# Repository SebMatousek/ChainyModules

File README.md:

# ChainyModules
An ecosystem of electronics modules based on the ESP32-C3FH4 microcontroller capable of chained communication through half-duplex UART.

This project is made to simplify the usage of different modules in robotics projects. Based on the microcontroller ESP32-C3FH4, which is powerfull enough for most tasks, different modules can be created, all the while allowing for chained connection (daisy chaining). Simply put, you can use these modules on different parts of your robot and interconnect them all using only 3 pins, and chain them together that only 1 cable needs to go to the main board (which can be a RPI, one of the modules themselves, ...).

Since all the modules use the same microcontroller, the programming is really easy and the communication as well -- the modules use half-duplex UART, the full-duplex UART from the ESP32 is transformed through a dual buffer open drain outputs. The absolute maximum speed for communication is 2,250,000 baud, but its better to use a bit less (1,000,000 baud works great and should be enough for most projects). For the programming of the boards, you can use the programming board specifically designed for this purpose so you don't have to connect 5 pins to each module separatly for programming.

The microcontroller has inbuilt flash for a smaller footprint on the board, and you can use WiFi or Bluetooth with it, it also has flash for storing user variables. It can also be connected to the computer directly without the need of a converter like the CP2102 (you may need to install a driver for it though).

Here are some more parameters:
|Chainy modules|v1.0|
|---|---|
| Microcontroller | ESP32-C3FH4 |
|Supply Voltage|3,3-12V|
|Communication pins|GND, VCC, TX|
|Maximum chained modules (limited by program only)|255|
|Broadcast ID|255|
|Currently designed modules|2|

### Instructions for using already existing modules
The already existing modules have their KiCAD schematic files in the Electronics/ folder. KiCAD 7.0.1 or newer is required, simply open the project and you should be able to plot the gerber files without having to modify anything.

The program is in the folder Software/ and is pretty simple. The basics for each module are the same and are in main.cpp. Every module has to be able to respond to the same basic commands (see table below). Specific modules then have different libraries with code to function. These libraries implement further commands, which have therefore preemptively been be added to the main.cpp switch statement.

|Command|cmd num|
|---|---|
|Set ID|1|
|Read type|2|
|Deepsleep*|3|

*Deepsleep is a command I implemented here because you can (and I did in one of my projects) use the power cables to also charge the robot when not running. Of course, this powers on the modules, so a module recognizes the charging (in my project that was simply using an LED and a photoresistor) and sends this command to the broadcasting address 255, so all the modules turn off. They then consume roughly 5 microamps so it doesn't slow down the charging nearly as much.

### Instructions for the custom servomotors
I created a custom servomotor capable of adressing and reading position, based on the MG90 servomotor. It uses the ChainyServo module board together with the two extension boards located inside the ChainyServo electronics folder. Using the picture in the ChainyServo Electronics folder, you can see how to assemble it. The STL and SLDPRT files are in the Mechanics/ folder. For the gears, motor and potentiometer, you can buy an MG90 (SG90 should work as well) servo and dissassemble it. When soldering the motor to the extension board, be careful that the dot on the plastic bottom of the motor has to align with the white arrow on the board, or the servo will rotate the other way and you will have to change the program. Also, beware that the motor can run on only about 5V, don't burn it - adjust the max pwm output accordingly!

I had my mechanical parts printed at JLCPCB with the material PA12.

#### Troubleshooting the servomotor
If the motor isn't spinning at all, most likely the mechanics is binding somewhere. Try to disassemble to servo and spin the gears manually a bit to see if you can find the problem.
If the motor spins but is going the wrong direction and won't stop jiggling, remove the biggest gear and flip it 180 degrees, which should fix the probelm (it can be inserted into the potentiometer in two ways but only one is correct).

### Instructions for creating a custom module
If you want to create a custom module to go with this repository, you are more than welcome to do so; and if you want send me the files and I can add them here, referencing you (pr not if you don't want me to).

To create a module that will be compatible, you have to mind these things the most:

|Dont't forget this|in your module|
|---|---|
| Microcontroller | ESP32-C3FH4 |
|Supply Voltage|3,3-12V*|
|Communication pins|GND, VCC, TX|
|Connectors|2x JST-PH|
|Programming pins (2mm connector)|VCC D+ D- BOOT GND**|
|Half duplex UART|at least 115 200 baud (ideally just use the buffer I have in my designs)|

*The range can be less if you want, but not more (or else you cannot use the modules already created). Ideally just use a regulator like the one in my modules.
** Or you can put a USB-C connector on the module but that's way too bulky and expensive for my liking.

Other than that, design what you like. You don't have to use my modules at all, as they probably don't fit your needs but that is fine --  the whole point of this project is to provide guidance on how to make such chained modules and to have some code and electronics done for it already, and over time hopefully create a whle ecosystem of these modules so that anyone can se what others have already designed and pick what souits them best. Have fun making, makers!

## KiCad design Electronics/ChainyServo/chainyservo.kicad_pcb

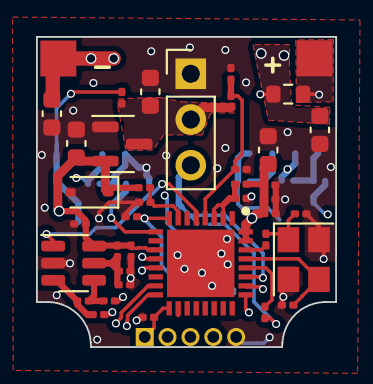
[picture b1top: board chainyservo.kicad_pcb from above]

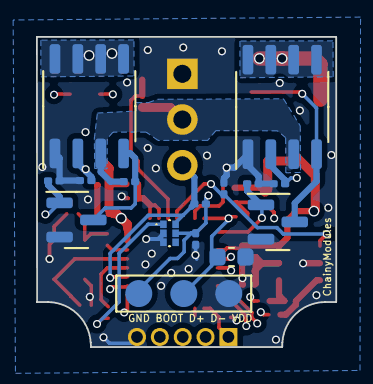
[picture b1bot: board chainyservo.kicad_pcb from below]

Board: 4 copper layers, 16.6 x 17.2 mm, 55 parts (15 on the bottom side), 29 nets.

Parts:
C1, C2, C7, C8, C9, C10, C13, C14, C17, C18, C19, C20: 100nF; C_0201_0603Metric
C3, C4: 27nF; C_0603_1608Metric
C5, C6, C21, C22: 2.2uF; C_0603_1608Metric
C11: 10nF; C_0201_0603Metric
C12: 1uF; C_0201_0603Metric
C15, C16: 16pF; C_0201_0603Metric
D1: BSD3C031V; D_SOD-323
IC1: ESP32-C3FH4; QFN50P500X500X90-33N-D
IC2: 74LVC2G07GM,132; PESD3V3L5UF115
J1: M+; Conn_pad_2x2mm
J2: Conn_01x03_Female; Pad_3_potentiometer
J3: Conn_01x03_Female; PinHeader_1x03_P2.54mm_Vertical
J4: Conn_01x05_Female; PinHeader_1x05_P1.27mm_Vertical
J5: M-; Conn_pad_2x2mm
L1: 2nH; L_0201_0603Metric
Q1, Q2: BSS138; SOT-23
R1, R3: 1k; R_0201_0603Metric
R2, R4, R5, R6, R10, R11, R15, R19: 22k; R_0201_0603Metric
R7: 10k; R_0201_0603Metric
R12, R14: 33R; R_0201_0603Metric
R13: 68m; R_0603_1608Metric
R16: 7k5; R_0201_0603Metric
R17: 0R; R_0201_0603Metric
R18: 499R; R_0201_0603Metric
U1, U2: WSP4606A; SOP-8_3.9x4.9mm_P1.27mm
U4: H7233-1; SOT-23
U5: INA181A1IDBVR; SOT-23-6
Y1: Crystal_GND23; Crystal_SMD_3225-4Pin_3.2x2.5mm

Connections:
+3V3: C2.1, C6.1, C9.1, C10.1, C11.1, C12.1, C13.1, C18.1, C21.1, D1.1 (K), IC1.11 (VDD3P3_RTC), IC1.17 (VDD3P3_CPU), IC1.31 (VDDA_1), IC1.32 (VDDA_2), IC2.5 (VCC), J2.1, J4.1, L1.1, R7.2, R10.1, R19.2, U4.2 (VO), U5.6 (V+)
AG1: IC1.9 (MTMS), Q1.1 (G), R5.1
AG2: IC1.16 (GPIO10), Q2.1 (G), R6.1
AMP: C20.1, IC1.5 (XTAL_32K_N), U5.1
BOOT: IC1.15 (GPIO9), J4.4
G1: Q1.3 (D), R1.2, U1.4 (G1)
G2: IC1.12 (MTCK), R2.1, U1.2 (G2)
G3: Q2.3 (D), R3.2, U2.4 (G1)
G4: IC1.13 (MTDO), R4.1, U2.2 (G2)
GND: C1.2, C2.2, C3.2, C4.2, C5.2, C6.2, C7.2, C9.2, C10.2, C11.2, C12.2, C13.2, C14.2, C15.2, C16.2, C17.2, C18.2, C19.2, C20.2, C21.2, C22.2, D1.2 (A), IC1.33 (GND), IC2.2 (GND), IC2.3 (2A), J2.3, J3.1, J4.5, Q1.2 (S), Q2.2 (S), R2.2, R4.2, R5.2, R6.2, R11.2, R16.2, U1.1 (S2), U2.1 (S2), U4.1 (GND), U5.2 (GND), Y1.2, Y1.4
M+: C4.1, R12.2, R13.1, U2.5 (D1), U2.6 (D1), U2.7 (D2), U2.8 (D2)
M-: C3.1, J5.1, U1.5 (D1), U1.6 (D1), U1.7 (D2), U1.8 (D2)
unnamed: C15.1, R17.2, Y1.1
unnamed: C17.1, IC1.7 (CHIP_EN), R19.1
unnamed: C14.1, IC1.2 (VDD3P3_1), IC1.3 (VDD3P3_2), L1.2
unnamed: IC2.1 (1A), R18.2
unnamed: J1.1, R13.2, R14.2
unnamed: C8.2, R14.1, U5.3 (+)
unnamed: C8.1, R12.1, U5.4 (-)
POT: C19.1, C22.1, IC1.8 (GPIO3), J2.2
REF: C7.1, R10.2, R11.1, U5.5 (REF)
RX: IC1.27 (U0RXD), IC2.6 (1Y), J3.3, R7.1
TX: IC1.28 (U0TXD), R18.1
USB_D+: IC1.26 (GPIO19), J4.2
USB_D-: IC1.25 (GPIO18), J4.3
VIN: C5.1, J3.2, R1.1, R3.1, R15.1, U1.3 (S1), U2.3 (S1), U4.3 (VI)
VM: C1.1, IC1.4 (XTAL_32K_P), R15.2, R16.1
XTAL_N: C16.1, IC1.29 (XTAL_N), Y1.3
XTAL_P: IC1.30 (XTAL_P), R17.1

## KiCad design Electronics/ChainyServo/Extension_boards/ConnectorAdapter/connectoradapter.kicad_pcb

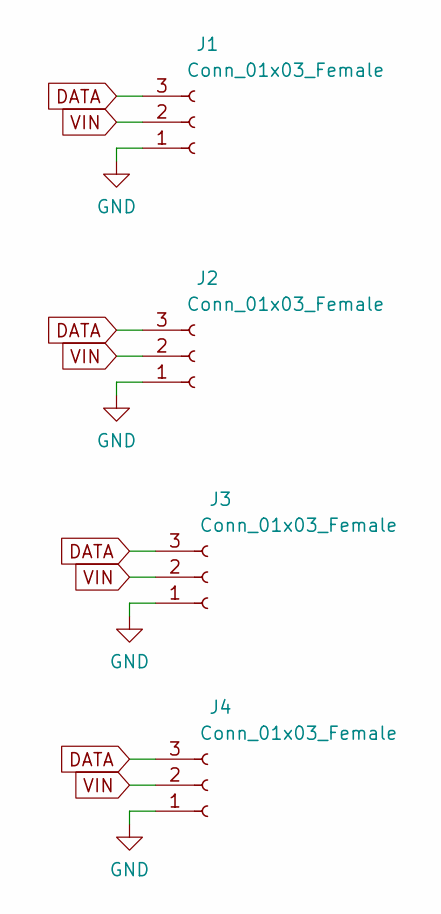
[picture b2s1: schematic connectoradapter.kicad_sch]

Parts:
J1: Conn_01x03_Female; PinHeader_1x03_P2.54mm_Vertical
J2, J3, J4: Conn_01x03_Female; JST_PH_S3B-PH-K_1x03_P2.00mm_Horizontal

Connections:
DATA: J1.3, J2.3, J3.3, J4.3
GND: J1.1, J2.1, J3.1, J4.1
VIN: J1.2, J2.2, J3.2, J4.2

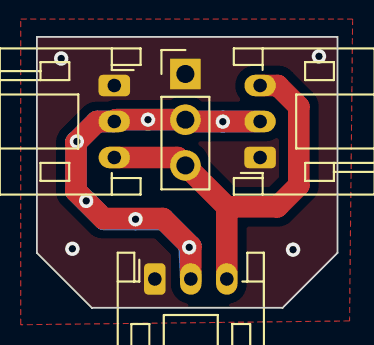
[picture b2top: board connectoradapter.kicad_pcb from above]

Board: 4 copper layers, 16.7 x 15.0 mm, 4 parts (0 on the bottom side), 3 nets.

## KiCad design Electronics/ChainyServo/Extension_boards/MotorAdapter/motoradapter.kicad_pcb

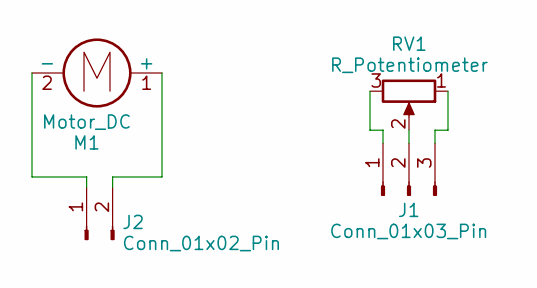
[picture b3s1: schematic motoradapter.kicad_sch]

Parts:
J1: Conn_01x03_Pin; PinHeader_1x03_P2.00mm_Vertical
J2: Conn_01x02_Pin; PinHeader_1x02_P2.00mm_Vertical
M1: Motor_DC; MG90I_motor
RV1: R_Potentiometer; MG90I_potentiometer

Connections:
unnamed: J1.1, RV1.3
unnamed: J1.2, RV1.2
unnamed: J1.3, RV1.1
unnamed: J2.1, M1.2 (-)
unnamed: J2.2, M1.1 (+)

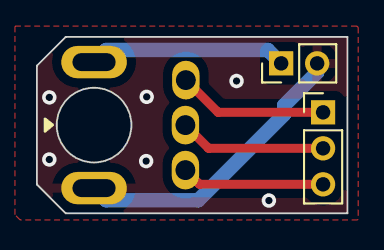
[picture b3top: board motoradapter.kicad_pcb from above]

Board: 4 copper layers, 17.2 x 9.8 mm, 4 parts (0 on the bottom side), 5 nets.

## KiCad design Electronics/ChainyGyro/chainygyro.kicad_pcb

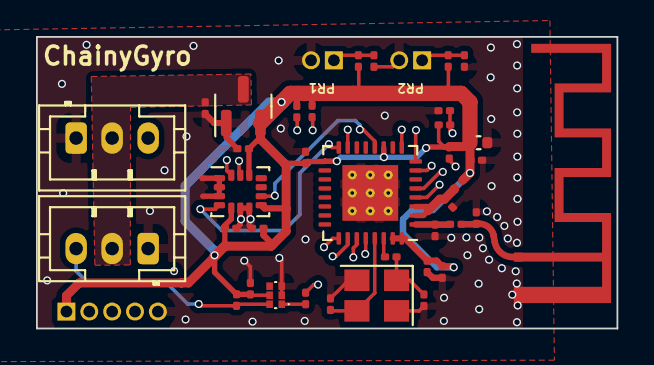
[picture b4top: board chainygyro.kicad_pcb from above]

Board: 4 copper layers, 32.2 x 16.2 mm, 40 parts (0 on the bottom side), 22 nets.

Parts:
AE1: PCB Antenna 2.4GHz 50Ohm; Texas_SWRA117D_2.4GHz_Left
C1, C3, C4, C6, C7, C12, C14, C17, C18, C19: 100nF; C_0201_0603Metric
C2: 10uF; C_0402_1005Metric
C5, C8: 16pF; C_0201_0603Metric
C9, C15, C16: 1uF; C_0201_0603Metric
C10: 10nF; C_0201_0603Metric
C11, C13: 3.3pF; C_0201_0603Metric
IC1: ESP32-C3FH4; QFN-32-1EP_5x5mm_P0.5mm_EP3.1x3.1mm_ThermalVias
IC2: 74LVC2G07GM,132; PESD3V3L5UF115
J1, J2: Conn_01x03_Female; JST_PH_B3B-PH-K_1x03_P2.00mm_Vertical
J3: Conn_01x05_Female; PinHeader_1x05_P1.27mm_Vertical
J4, J5: Conn_01x02_Socket; PinHeader_1x02_P1.27mm_Vertical
L1: 2nH; L_0201_0603Metric
L2: 2.2nH; L_0201_0603Metric
R1: 0R; R_0201_0603Metric
R2: 22k; R_0201_0603Metric
R3, R4, R6, R7, R8: 10k; R_0201_0603Metric
R5: 499R; R_0201_0603Metric
U1: H7233-1; SOT-23
U2: LSM6DS3TR-C; LGA-14_3x2.5mm_P0.5mm_LayoutBorder3x4y
Y1: Crystal_GND23; Crystal_SMD_3225-4Pin_3.2x2.5mm

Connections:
+3V3: C2.1, C4.1, C9.1, C10.1, C12.1, C14.1, C16.1, C17.1, C18.1, C19.1, IC1.11 (VDD3P3_RTC), IC1.17 (VDD3P3_CPU), IC1.31 (VDDA_1), IC1.32 (VDDA_2), IC2.5 (VCC), J3.1, L1.1, R2.2, R3.1, R4.1, R6.2, R7.1, R8.1, U1.2 (VO), U2.5 (VDDIO), U2.8 (VDD), U2.12 (CS)
BOOT: IC1.15 (GPIO9), J3.4
GND: AE1.1, C1.2, C2.2, C3.2, C4.2, C5.2, C6.2, C7.2, C8.2, C9.2, C10.2, C11.2, C12.2, C13.2, C14.2, C15.2, C16.2, C17.2, C18.2, C19.2, IC1.33 (GND), IC2.2 (GND), IC2.3 (2A), J1.1, J2.1, J3.5, J4.2, J5.2, U1.1 (GND), U2.1 (SDO/SA0), U2.2 (SDX), U2.3 (SCX), U2.6 (GND), U2.7 (GND), Y1.2, Y1.4
INT1: IC1.16 (GPIO10), U2.4 (INT1)
INT2: IC1.12 (MTCK), U2.9 (INT2)
LNA: C11.1, IC1.1 (LNA_IN), L2.1
unnamed: AE1.2, C13.1, L2.2
unnamed: C5.1, R1.2, Y1.1
unnamed: C7.1, IC1.7 (CHIP_EN), R2.1
unnamed: C6.1, IC1.2 (VDD3P3_1), IC1.3 (VDD3P3_2), L1.2
unnamed: IC2.1 (1A), R5.2
PR1: C1.1, IC1.9 (MTMS), J5.1, R4.2
PR2: C3.1, IC1.8 (GPIO3), J4.1, R3.2
RX: IC1.27 (U0RXD), IC2.6 (1Y), J1.3, J2.3, R6.1
SCL: IC1.4 (XTAL_32K_P), R7.2, U2.13 (SCL)
SDA: IC1.5 (XTAL_32K_N), R8.2, U2.14 (SDA)
TX: IC1.28 (U0TXD), R5.1
USB_D+: IC1.26 (GPIO19), J3.2
USB_D-: IC1.25 (GPIO18), J3.3
VIN: C15.1, J1.2, J2.2, U1.3 (VI)
XTAL_N: C8.1, IC1.29 (XTAL_N), Y1.3
XTAL_P: IC1.30 (XTAL_P), R1.1

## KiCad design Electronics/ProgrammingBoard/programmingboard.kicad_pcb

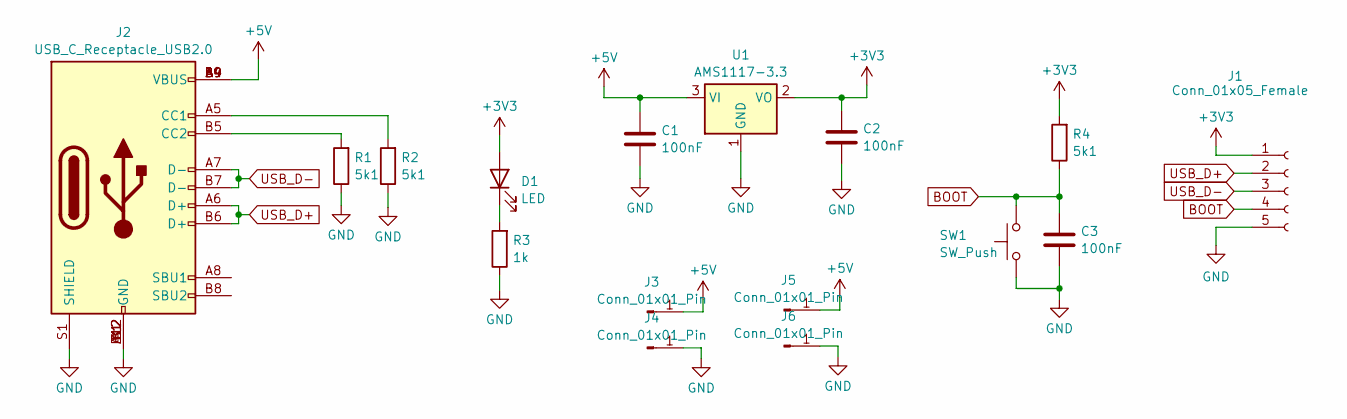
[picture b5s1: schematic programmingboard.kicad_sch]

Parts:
C1, C2, C3: 100nF; C_1206_3216Metric_Pad1.33x1.80mm_HandSolder
D1: LED; D_1206_3216Metric_Pad1.42x1.75mm_HandSolder
J1: Conn_01x05_Female; PinHeader_1x05_P1.27mm_Vertical
J2: USB_C_Receptacle_USB2.0; USB_C_Receptacle_GCT_USB4105-xx-A_16P_TopMnt_Horizontal; LCSC C393939
J3, J4, J5, J6: Conn_01x01_Pin; PinHeader_1x01_P2.54mm_Vertical
R1, R2, R4: 5k1; R_1206_3216Metric_Pad1.30x1.75mm_HandSolder
R3: 1k; R_1206_3216Metric_Pad1.30x1.75mm_HandSolder
SW1: SW_Push; SW_PUSH_6mm_H5mm
U1: AMS1117-3.3; SOT-223-3_TabPin2

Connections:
+3V3: C2.1, D1.2 (A), J1.1, R4.2, U1.2 (VO)
+5V: C1.1, J2.A4 (VBUS), J2.A9 (VBUS), J2.B4 (VBUS), J2.B9 (VBUS), J3.1, J5.1, U1.3 (VI)
BOOT: C3.1, J1.4, R4.1, SW1.2
GND: C1.2, C2.2, C3.2, J1.5, J2.A1 (GND), J2.A12 (GND), J2.B1 (GND), J2.B12 (GND), J2.S1 (SHIELD), J4.1, J6.1, R1.1, R2.1, R3.1, SW1.1, U1.1 (GND)
unnamed: D1.1 (K), R3.2
unnamed: J2.A5 (CC1), R2.2
unnamed: J2.B5 (CC2), R1.2
USB_D+: J1.2, J2.A6 (D+), J2.B6 (D+)
USB_D-: J1.3, J2.A7 (D-), J2.B7 (D-)

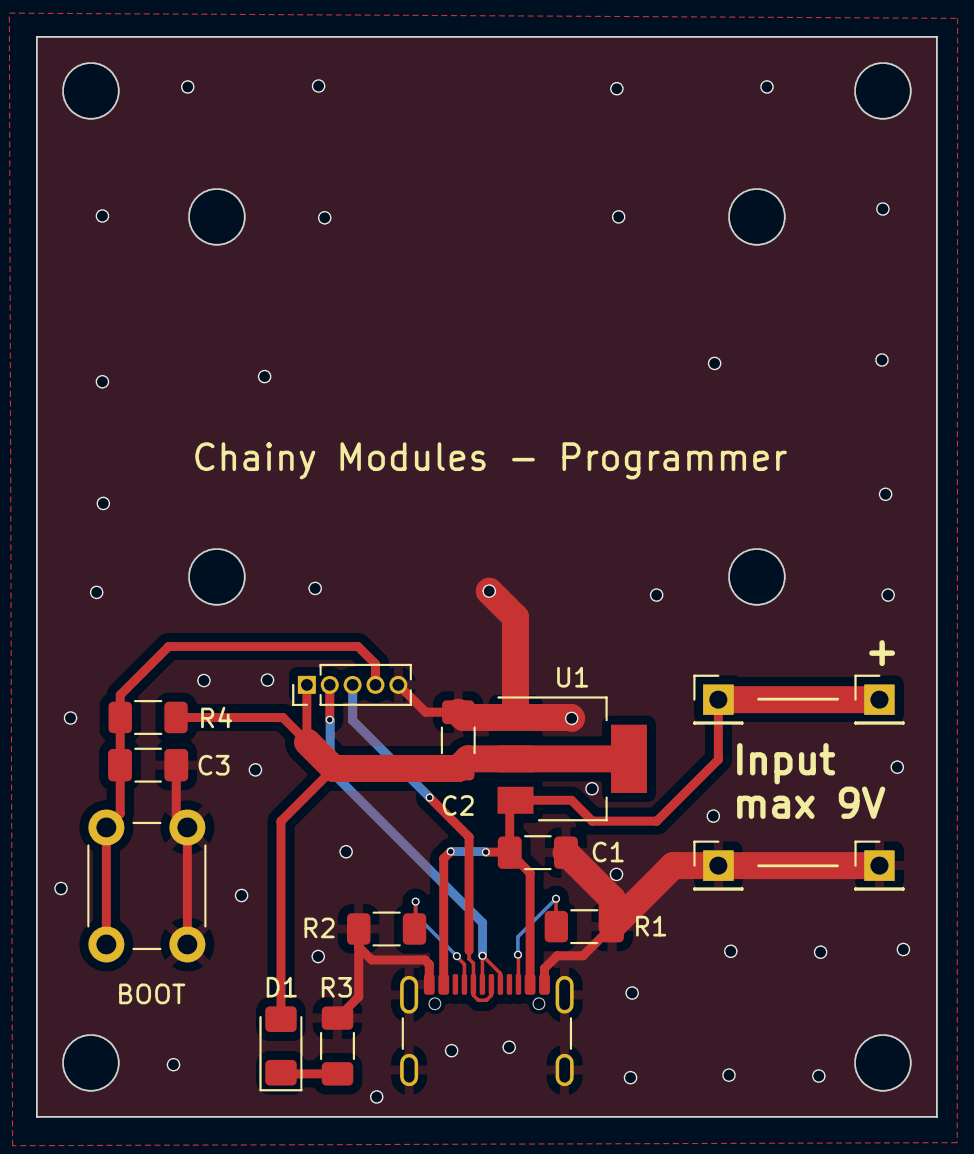
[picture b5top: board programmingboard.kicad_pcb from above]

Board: 2 copper layers, 50.0 x 60.0 mm, 16 parts (0 on the bottom side), 9 nets.

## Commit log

2024-01-27 Added readme + license, and two modules - servo and gyro. Also added the programming board.
